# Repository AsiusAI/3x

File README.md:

# Asius 3X

```
git clone https://github.com/AsiusAI/3x
cd 3x
git submodule update --init --recursive
```

## Install ubuntu rockchip

https://github.com/Joshua-Riek/ubuntu-rockchip/releases/download/v2.4.0/ubuntu-24.04-preinstalled-server-arm64-orangepi-5-max.img.xz

flash this with Balena Etcher to the M.2 SSD. The Max version is okay for Ultra, the only difference should be the HDMI input/output port

ubuntu-24.04-preinstalled-server-arm64-orangepi-5-max.img

## Getting OV13855 camera working

See what overlays exist I used `orangepi-5-max-cam1.dtbo` overlay

```
# Check what devices exist, should have orangepi-5-max-cam1.dtbo overlay
ls /usr/lib/firmware/6.1.0-1025-rockchip/device-tree/rockchip/overlay | grep cam1

sudo nano /etc/default/u-boot

# Edit this line
# U_BOOT_FDT_OVERLAYS="device-tree/rockchip/overlay/orangepi-5-max-cam0.dtbo device-tree/rockchip/overlay/orangepi-5-max-cam1.dtbo device-tree/rockchip/overlay/orangepi-5-max-cam2.dtbo"

sudo u-boot-update

sudo reboot

# See if finds cameras
dmesg | grep ov13855
# Should show something like `Detected OV00d855 sensor, REVISION 0xb0`

# Get test image
sudo apt install v4l-utils -y
# To find the device use `v4l2-ctl --list-devices` (the first dev from rkisp_mainpath)
v4l2-ctl -d /dev/video33 --set-fmt-video=width=4224,height=3136,pixelformat='NV12' --stream-mmap --stream-skip=10 --stream-count=1 --stream-to=processed.yuv && ffmpeg -f rawvideo -pix_fmt nv12 -s 4224x3136 -i processed.yuv -y img.jpg
```

Install multimedia

sudo add-apt-repository ppa:liujianfeng1994/rockchip-multimedia
sudo apt update
sudo apt install rockchip-multimedia-config

sudo add-apt-repository ppa:jjriek/rockchip-multimedia
sudo apt update
sudo apt install camera-engine-rkaiq-rk3588

## For building Armbian OS

```
git clone https://github.com/armbian/build && cd armbian-build

./compile.sh BOARD=orangepi5-max RELEASE=noble BUILD_DESKTOP=yes DESKTOP_ENVIRONMENT=xfce DESKTOP_APPGROUPS_SELECTED='' DESKTOP_ENVIRONMENT_CONFIG_NAME=config_base BRANCH=vendor NETWORKING_STACK="network-manager" PREFER_DOCKER=no KERNEL_CONFIGURE=no
sudo dd if=output/images/Armbian-unofficial_25.11.0-trunk_Orangepi5-max_noble_vendor_6.1.115_xfce_desktop.img of=/dev/sda bs=4M status=progress conv=fsync
```

## A

cp orangepi-5-imx415-c1.dtbo /usr/lib/firmware/6.1.0-1025-rockchip/device-tree/rockchip/overlay

/usr/lib/firmware/6.1.0-1025-rockchip/device-tree/rockchip/rk3588-orangepi-5-max.dtb

device-tree/rockchip/overlay/orangepi-5-max-cam0.dtbo
device-tree/rockchip/overlay/orangepi-5-max-cam1.dtbo
device-tree/rockchip/overlay/orangepi-5-max-cam2.dtbo

sudo ./build.sh --suite noble --flavor desktop --board orangepi-5-max

## Getting openpilot to work

./tools/op.sh setup

./tools/op.sh venv

sudo apt update
sudo apt install libx11-dev libxcursor-dev libxrandr-dev libxi-dev libxinerama-dev
cd ~/3x/openpilot/third_party/raylib && ./build.sh

./tools/op.sh build

./launch_openpilot.sh

## OP working

sudo apt update

git clone https://github.com/asius.ai/3x
cd 3x
git submodule update --init --recursive openpilot
cd openpilot
./tools/op.sh setup
./tools/op.sh venv

sudo apt install libx11-dev libxcursor-dev libxrandr-dev libxi-dev libxinerama-dev
./third_party/raylib/build.sh

./tools/op.sh build

mkdir -p /home/orangepi/.comma/persist/comma/ && ssh-keygen -t rsa -N "" -f /home/orangepi/.comma/persist/comma/id_rsa

sudo apt install tmux

sudo mkdir /data && sudo chown ubuntu /data

sudo apt install xserver-xorg openbox xterm mesa-utils xinit

# tinygrad GPU=1 (on armbian)

wget -qO - https://download.opensuse.org/repositories/home:/amazingfate:/panfork-mesa/Debian_12/Release.key | sudo gpg --dearmor -o /etc/apt/trusted.gpg.d/panfork-mesa.gpg

echo "deb [trusted=yes] https://download.opensuse.org/repositories/home:/amazingfate:/panfork-mesa/Debian_12/ /" | sudo tee /etc/apt/sources.list.d/panfork-mesa.list

or `sudo add-apt-repository ppa:liujianfeng1994/panfork-mesa` ???

sudo apt update

sudo apt install mali-g610-firmware libmali-g610-x11

clinfo

# OS problems

## Orange Pi 1.0.0 Jammy with Linux 5.10.160-rockchip-rk3588 from OrangePi website

Pros:
- desktop with display works
- openpilot with panda works
- GPU=1 works in tinygrad

Cons:
- can't get any image from cameras, but they are recognized in dmesg
- larger OS
- no way to build it myself
- no community support

## ubuntu-rockchip

Pros:
- can build it myself (although it takes very long)
- cameras work fine, even IMX415
- not sure but maybe even openpilot worked

Cons:
- development stopped
- large OS
- build

## Armbian

Pros:
- build easy and fast
- small OS
- will receive updates
- openpilot works with webcam, GPU=1 works

Cons:
- cameras not working (because rkif and rkisp don't exist)

## RKNN yolov8 example working

cd ~/rknn_model_zoo/examples/yolov8

pip install rknn-toolkit2

./model/download_model.sh

cd python && python convert.py ../model/yolov8n.onnx rk3588

wget https://github.com/rockchip-linux/rknpu2/raw/refs/heads/master/runtime/RK3588/Linux/librknn_api/aarch64/librknnrt.so && sudo mv librknnrt.so /usr/lib/

python yolov8.py --model_path ../model/yolov8.rknn --target rk3588

output: ~/rknn_model_zoo/examples/yolov8/result.png

## Armbian camera support is broken

see these issues:
https://github.com/armbian/linux-rockchip/issues/164
https://github.com/armbian/linux-rockchip/issues/246
https://forum.radxa.com/t/dev-video-01/20490/42

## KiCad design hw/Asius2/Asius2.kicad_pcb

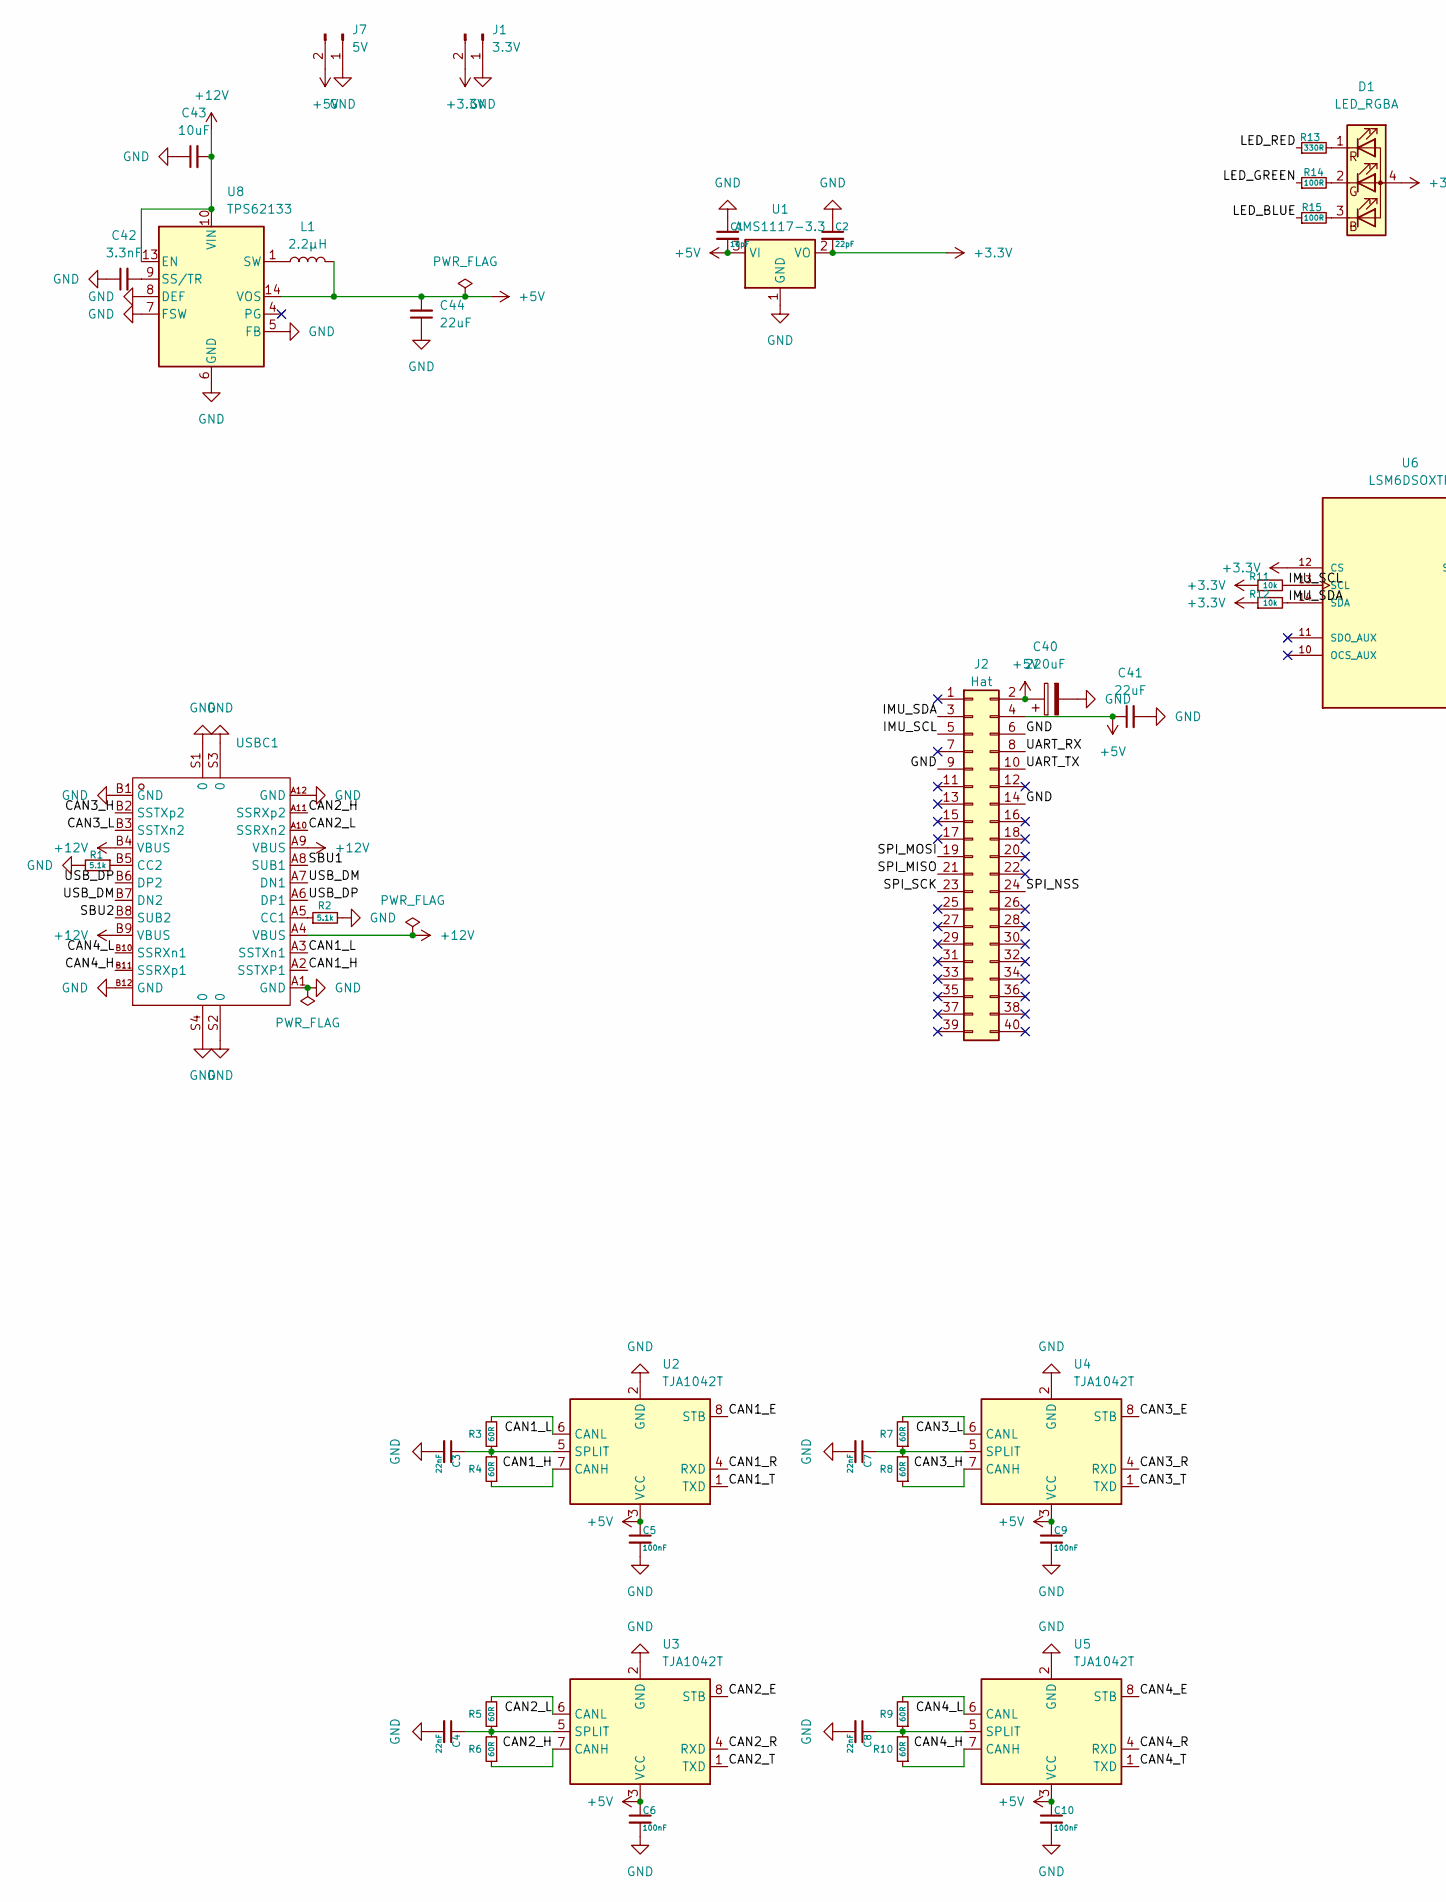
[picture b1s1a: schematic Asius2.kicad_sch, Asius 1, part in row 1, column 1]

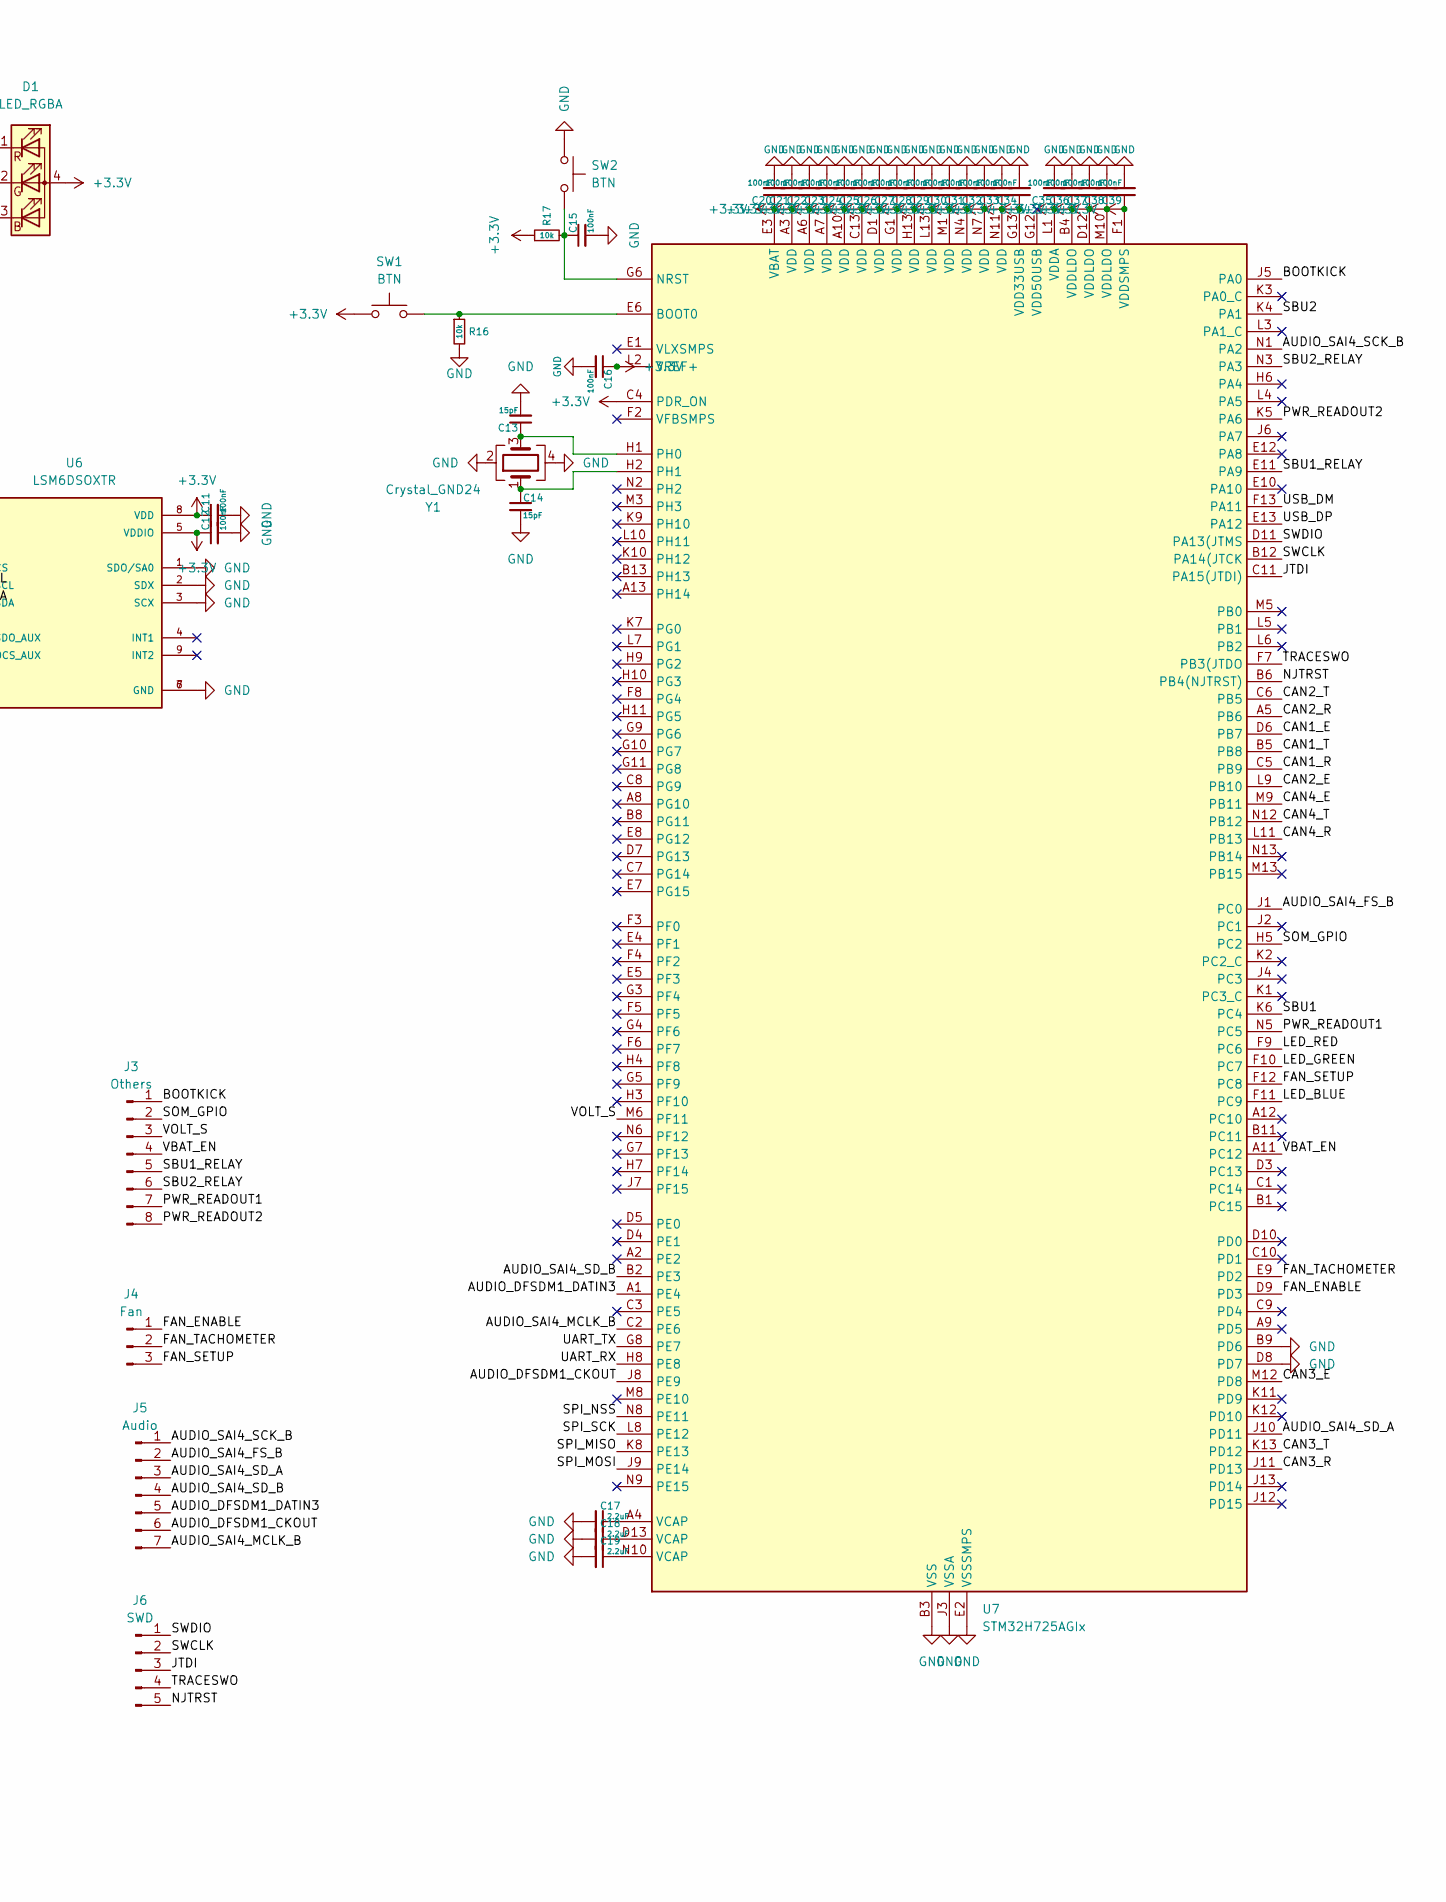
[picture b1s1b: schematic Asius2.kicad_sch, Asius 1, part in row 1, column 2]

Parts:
C1: 10pF; C_0603_1608Metric; MFR.Part # CC0603JRNPO9BN100; JLCPCB Part # C106245
C2: 22pF; C_0603_1608Metric; MFR.Part # CC0603JRNPO9BN220; JLCPCB Part # C105620
C3, C4, C7, C8: 22nF; C_0603_1608Metric; MFR.Part # CC0603KRX7R8BB223; JLCPCB Part # C106217
C5, C6, C9, C10, C11, C12, C15, C16, C20, C21, C22, C23, C24, C25, C26, C27, C28, C29, C30, C31, C32, C33, C34, C35, C36, C37, C38, C39: 100nF; C_0603_1608Metric; MFR.Part # CC0603KRX7R9BB104; JLCPCB Part # C14663
C13, C14: 15pF; C_0603_1608Metric; MFR.Part # CC0603JRNPO9BN150; JLCPCB Part # C107037
C17, C18, C19: 2.2uF; C_0603_1608Metric; MFR.Part # CC0603KRX5R6BB225; JLCPCB Part # C106213
C40: 220uF; CP_Elec_6.3x5.4; MFR.Part # RVT1A221M0605; JLCPCB Part # C3345
C41, C44: 22uF; C_0603_1608Metric; MFR.Part # CC0603MRX5R5BB226; JLCPCB Part # C109448
C42: 3.3nF; C_0603_1608Metric; MFR.Part # CC0603JRNPO9BN332; JLCPCB Part # C107048
C43: 10uF; C_0805_2012Metric; MFR.Part # CC0805KKX5R8BB106; JLCPCB Part # C89831
D1: LED_RGBA; LED_RGB_1210; MFR.Part # SZYY1209RGB-B 4pin; JLCPCB Part # C3029073
J1: 3.3V; PinHeader_1x02_P2.54mm_Vertical
J2: Hat; PinHeader_2x20_P2.54mm_Vertical
J3: Others; PinHeader_1x08_P2.54mm_Vertical
J4: Fan; PinHeader_1x03_P2.54mm_Vertical
J5: Audio; PinHeader_1x07_P2.54mm_Vertical
J6: SWD; PinHeader_1x05_P2.54mm_Vertical
J7: 5V; PinHeader_1x02_P2.54mm_Vertical
L1: 2.2µH; L_Coilcraft_XxL4020; MFR.Part # XFL4020-222MEC; JLCPCB Part # C122469
R1, R2: 5.1k; R_0603_1608Metric; MFR.Part # RT0603BRD075K1L; JLCPCB Part # C122969
R3, R4, R5, R6, R7, R8, R9, R10: 60R; R_0603_1608Metric; MFR.Part # RC0603FR-0762RL; JLCPCB Part # C245989
R11, R12, R16, R17: 10k; R_0603_1608Metric; MFR.Part # RC0603FR-0710KL; JLCPCB Part # C98220
R13: 330R; R_0603_1608Metric; MFR.Part # RC0603FR-07330RL; JLCPCB Part # C105881
R14, R15: 100R; R_0603_1608Metric; MFR.Part # RC0603FR-07100RL; JLCPCB Part # C105588
SW1, SW2: BTN; SW_SPST_EVQP2_ShortPushTravel_H2.1mm; MFR.Part # EVQP2R02M; JLCPCB Part # C79161
U1: AMS1117-3.3; SOT-223-3_TabPin2; MFR.Part # AMS1117-3.3; JLCPCB Part # C6186
U2, U3, U4, U5: TJA1042T; SOIC-8_3.9x4.9mm_P1.27mm; MFR.Part # TJA1042T/1J; JLCPCB Part # C53670
U6: LSM6DSOXTR; PQFN50P250X300X86-14N; PARTREV 3.0; JLCPCB Part # C481766
U7: STM32H725AGIx; UFBGA-169_7x7mm_Layout13x13_P0.5mm; MFR.Part # STM32H725AGI6; JLCPCB Part # C730148
U8: TPS62133; VQFN-16-1EP_3x3mm_P0.5mm_EP1.68x1.68mm_ThermalVias; MFR.Part # TPS62133RGTR; JLCPCB Part # C73973
USBC1: USB-C-SMD_TYPE-C-USB-20; Manufacturer Part TYPE-C-31-M-04; LCSC Part Name Type-C 母
Y1: Crystal_GND24; Crystal_SMD_3225-4Pin_3.2x2.5mm; MFR.Part # X322525MOB4SI; JLCPCB Part # C9006

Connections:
+3.3V: C2.2, C11.1, C12.1, C16.1, C20.1, C21.1, C22.1, C23.1, C24.1, C25.1, C26.1, C27.1, C28.1, C29.1, C30.1, C31.1, C32.1, C33.1, C34.1, C35.1, C36.1, C37.1, C38.1, C39.1, D1.4 (A), J1.2, R11.1, R12.1, R17.1, SW1.1, U1.2 (VO), U6.5 (VDDIO), U6.8 (VDD), U6.12 (CS), U7.A3 (VDD), U7.A6 (VDD), U7.A7 (VDD), U7.A10 (VDD), U7.B4 (VDDLDO), U7.C4 (PDR_ON), U7.C13 (VDD), U7.D1 (VDD), U7.D12 (VDDLDO), U7.E3 (VBAT), U7.F1 (VDDSMPS), U7.G1 (VDD), U7.G13 (VDD33USB), U7.H13 (VDD), U7.L1 (VDDA), U7.L2 (VREF+), U7.L13 (VDD), U7.M1 (VDD), U7.M10 (VDDLDO), U7.N4 (VDD), U7.N7 (VDD), U7.N11 (VDD)
+5V: C1.2, C5.1, C6.1, C9.1, C10.1, C40.1, C41.1, C44.2, J2.2, J2.4, J7.2, L1.2, U1.3 (VI), U2.3 (VCC), U3.3 (VCC), U4.3 (VCC), U5.3 (VCC), U8.14 (VOS)
+12V: C43.2, U8.10 (VIN), U8.11 (VIN), U8.12 (VIN), U8.13 (EN), USBC1.A4 (VBUS), USBC1.A9 (VBUS), USBC1.B4 (VBUS), USBC1.B9 (VBUS)
/AUDIO_DFSDM1_CKOUT: J5.6, U7.J8 (PE9)
/AUDIO_DFSDM1_DATIN3: J5.5, U7.A1 (PE4)
/AUDIO_SAI4_FS_B: J5.2, U7.J1 (PC0)
/AUDIO_SAI4_MCLK_B: J5.7, U7.C2 (PE6)
/AUDIO_SAI4_SCK_B: J5.1, U7.N1 (PA2)
/AUDIO_SAI4_SD_A: J5.3, U7.J10 (PD11)
/AUDIO_SAI4_SD_B: J5.4, U7.B2 (PE3)
/BOOTKICK: J3.1, U7.J5 (PA0)
/CAN1_E: U2.8 (STB), U7.D6 (PB7)
/CAN1_H: R4.1, U2.7 (CANH), USBC1.A2 (SSTXP1)
/CAN1_L: R3.2, U2.6 (CANL), USBC1.A3 (SSTXn1)
/CAN1_R: U2.4 (RXD), U7.C5 (PB9)
/CAN1_T: U2.1 (TXD), U7.B5 (PB8)
/CAN2_E: U3.8 (STB), U7.L9 (PB10)
/CAN2_H: R6.1, U3.7 (CANH), USBC1.A11 (SSRXp2)
/CAN2_L: R5.2, U3.6 (CANL), USBC1.A10 (SSRXn2)
/CAN2_R: U3.4 (RXD), U7.A5 (PB6)
/CAN2_T: U3.1 (TXD), U7.C6 (PB5)
/CAN3_E: U4.8 (STB), U7.M12 (PD8)
/CAN3_H: R8.1, U4.7 (CANH), USBC1.B2 (SSTXp2)
/CAN3_L: R7.2, U4.6 (CANL), USBC1.B3 (SSTXn2)
/CAN3_R: U4.4 (RXD), U7.J11 (PD13)
/CAN3_T: U4.1 (TXD), U7.K13 (PD12)
/CAN4_E: U5.8 (STB), U7.M9 (PB11)
/CAN4_H: R10.1, U5.7 (CANH), USBC1.B11 (SSRXp1)
/CAN4_L: R9.2, U5.6 (CANL), USBC1.B10 (SSRXn1)
/CAN4_R: U5.4 (RXD), U7.L11 (PB13)
/CAN4_T: U5.1 (TXD), U7.N12 (PB12)
/FAN_ENABLE: J4.1, U7.D9 (PD3)
/FAN_SETUP: J4.3, U7.F12 (PC8)
/FAN_TACHOMETER: J4.2, U7.E9 (PD2)
/IMU_SCL: J2.5, R11.2, U6.13 (SCL)
/IMU_SDA: J2.3, R12.2, U6.14 (SDA)
/JTDI: J6.3, U7.C11 (PA15(JTDI))
/LED_BLUE: R15.1, U7.F11 (PC9)
/LED_GREEN: R14.1, U7.F10 (PC7)
/LED_RED: R13.1, U7.F9 (PC6)
/NJTRST: J6.5, U7.B6 (PB4(NJTRST))
/PWR_READOUT1: J3.7, U7.N5 (PC5)
/PWR_READOUT2: J3.8, U7.K5 (PA6)
/SBU1: U7.K6 (PC4), USBC1.A8 (SUB1)
/SBU1_RELAY: J3.5, U7.E11 (PA9)
/SBU2: U7.K4 (PA1), USBC1.B8 (SUB2)
/SBU2_RELAY: J3.6, U7.N3 (PA3)
/SOM_GPIO: J3.2, U7.H5 (PC2)
/SPI_MISO: J2.21, U7.K8 (PE13)
/SPI_MOSI: J2.19, U7.J9 (PE14)
/SPI_NSS: J2.24, U7.N8 (PE11)
/SPI_SCK: J2.23, U7.L8 (PE12)
/SWCLK: J6.2, U7.B12 (PA14(JTCK)
/SWDIO: J6.1, U7.D11 (PA13(JTMS)
/TRACESWO: J6.4, U7.F7 (PB3(JTDO)
/UART_RX: J2.8, U7.H8 (PE8)
/UART_TX: J2.10, U7.G8 (PE7)
/USB_DM: U7.F13 (PA11), USBC1.A7 (DN1), USBC1.B7 (DN2)
/USB_DP: U7.E13 (PA12), USBC1.A6 (DP1), USBC1.B6 (DP2)
/VBAT_EN: J3.4, U7.A11 (PC12)
/VOLT_S: J3.3, U7.M6 (PF11)
GND: C1.1, C2.1, C3.2, C4.2, C5.2, C6.2, C7.2, C8.2, C9.2, C10.2, C11.2, C12.2, C13.2, C14.2, C15.2, C16.2, C17.2, C18.2, C19.2, C20.2, C21.2, C22.2, C23.2, C24.2, C25.2, C26.2, C27.2, C28.2, C29.2, C30.2, C31.2, C32.2, C33.2, C34.2, C35.2, C36.2, C37.2, C38.2, C39.2, C40.2, C41.2, C42.1, C43.1, C44.1, J1.1, J2.6, J2.9, J2.14, J7.1, R1.2, R2.2, R16.2, SW2.1, U1.1 (GND), U2.2 (GND), U3.2 (GND), U4.2 (GND), U5.2 (GND), U6.1 (SDO/SA0), U6.2 (SDX), U6.3 (SCX), U6.6 (GND), U6.7 (GND), U7.B3 (VSS), U7.B7 (VSS), U7.B9 (PD6), U7.B10 (VSS), U7.C12 (VSS), U7.D2 (VSS), U7.D8 (PD7), U7.E2 (VSSSMPS), U7.G2 (VSS), U7.H12 (VSS), U7.J3 (VSSA), U7.L12 (VSS), U7.M2 (VSS), U7.M4 (VSS), U7.M7 (VSS), U7.M11 (VSS), U8.5 (FB), U8.6 (GND), U8.7 (FSW), U8.8 (DEF), U8.15 (GND), U8.16 (GND), U8.17 (GND), USBC1.A1 (GND), USBC1.A12 (GND), USBC1.B1 (GND), USBC1.B12 (GND), USBC1.S1 (0), USBC1.S2 (0), USBC1.S3 (0), USBC1.S4 (0), Y1.2, Y1.4
unnamed: C17.1, U7.A4 (VCAP)
unnamed: C18.1, U7.D13 (VCAP)
unnamed: C19.1, U7.N10 (VCAP)
unnamed: D1.3 (BK), R15.2
unnamed: D1.2 (GK), R14.2
unnamed: D1.1 (RK), R13.2
unnamed: L1.1, U8.1 (SW), U8.2 (SW), U8.3 (SW)
unnamed: C3.1, R3.1, R4.2, U2.5 (SPLIT)
unnamed: C4.1, R5.1, R6.2, U3.5 (SPLIT)
unnamed: C7.1, R7.1, R8.2, U4.5 (SPLIT)
unnamed: C8.1, R9.1, R10.2, U5.5 (SPLIT)
unnamed: R16.1, SW1.2, U7.E6 (BOOT0)
unnamed: C15.1, R17.2, SW2.2, U7.G6 (NRST)
unnamed: C13.1, U7.H1 (PH0), Y1.3
unnamed: C14.1, U7.H2 (PH1), Y1.1
unnamed: C42.2, U8.9 (SS/TR)
unnamed: R2.1, USBC1.A5 (CC1)
unnamed: R1.1, USBC1.B5 (CC2)

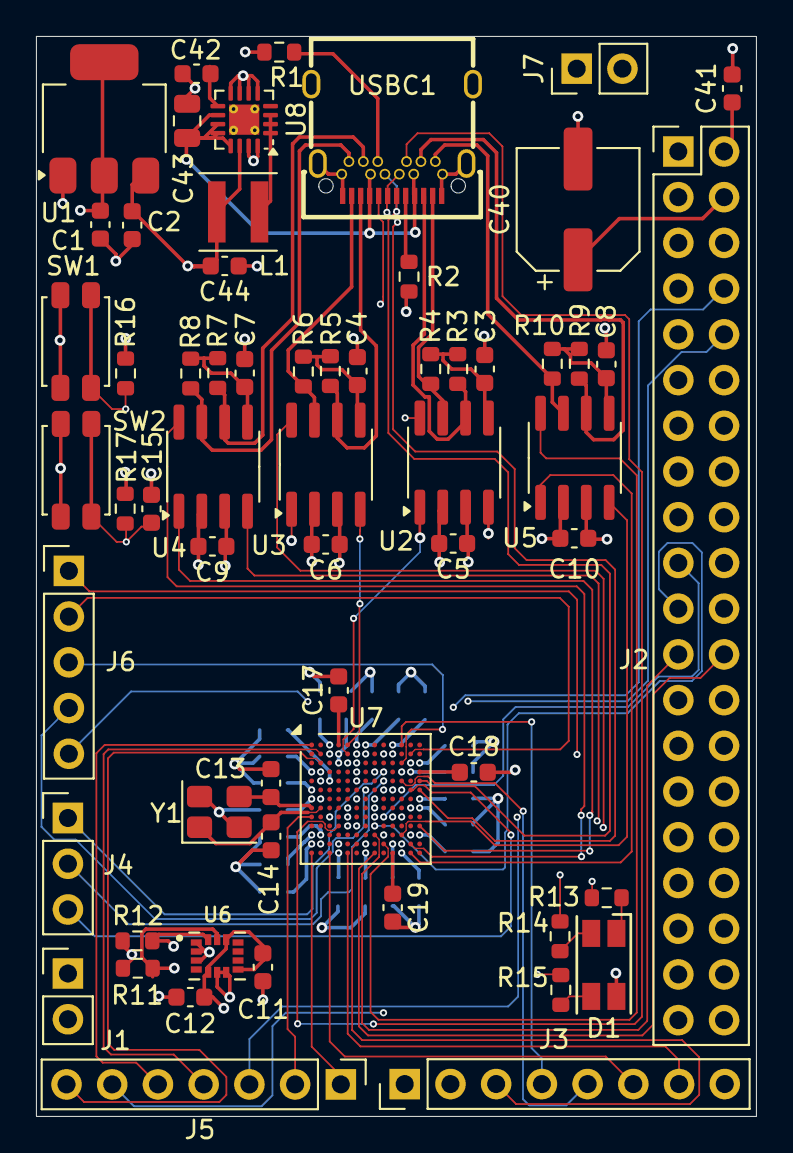
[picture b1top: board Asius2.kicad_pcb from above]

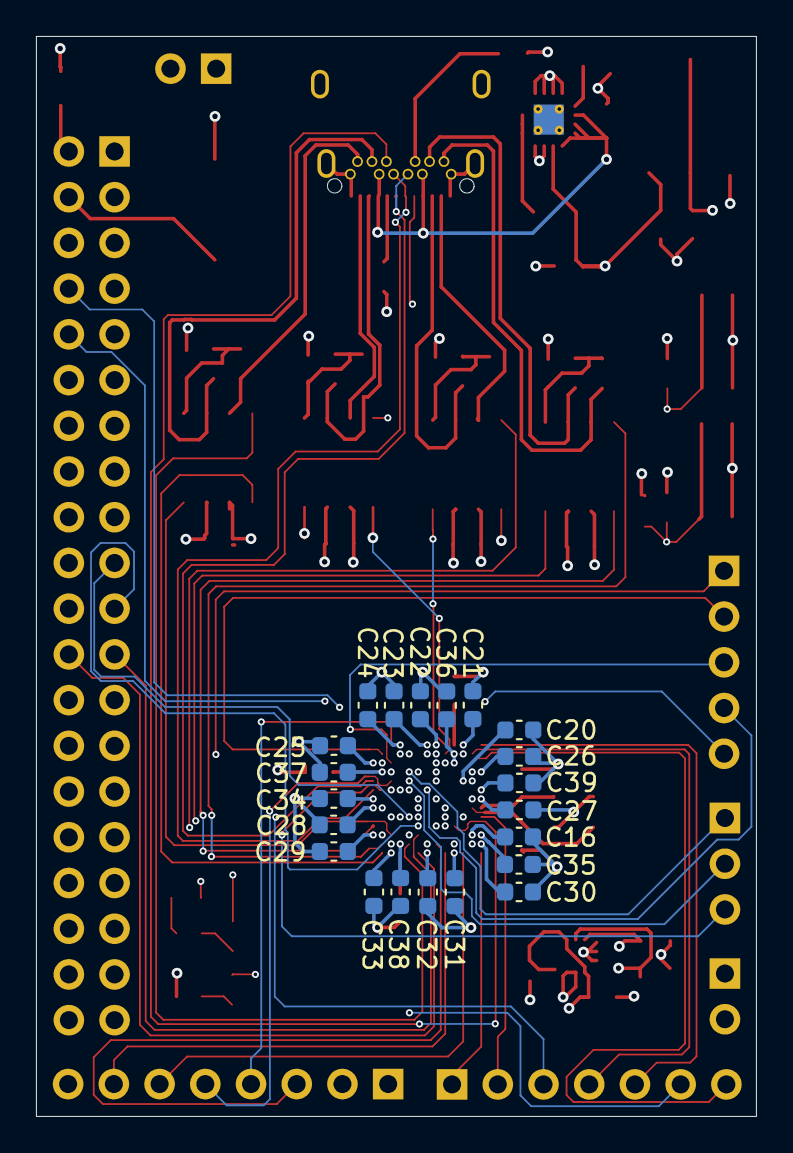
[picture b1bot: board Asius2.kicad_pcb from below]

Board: 6 copper layers, 40.0 x 60.0 mm, 82 parts (21 on the bottom side), 80 nets.

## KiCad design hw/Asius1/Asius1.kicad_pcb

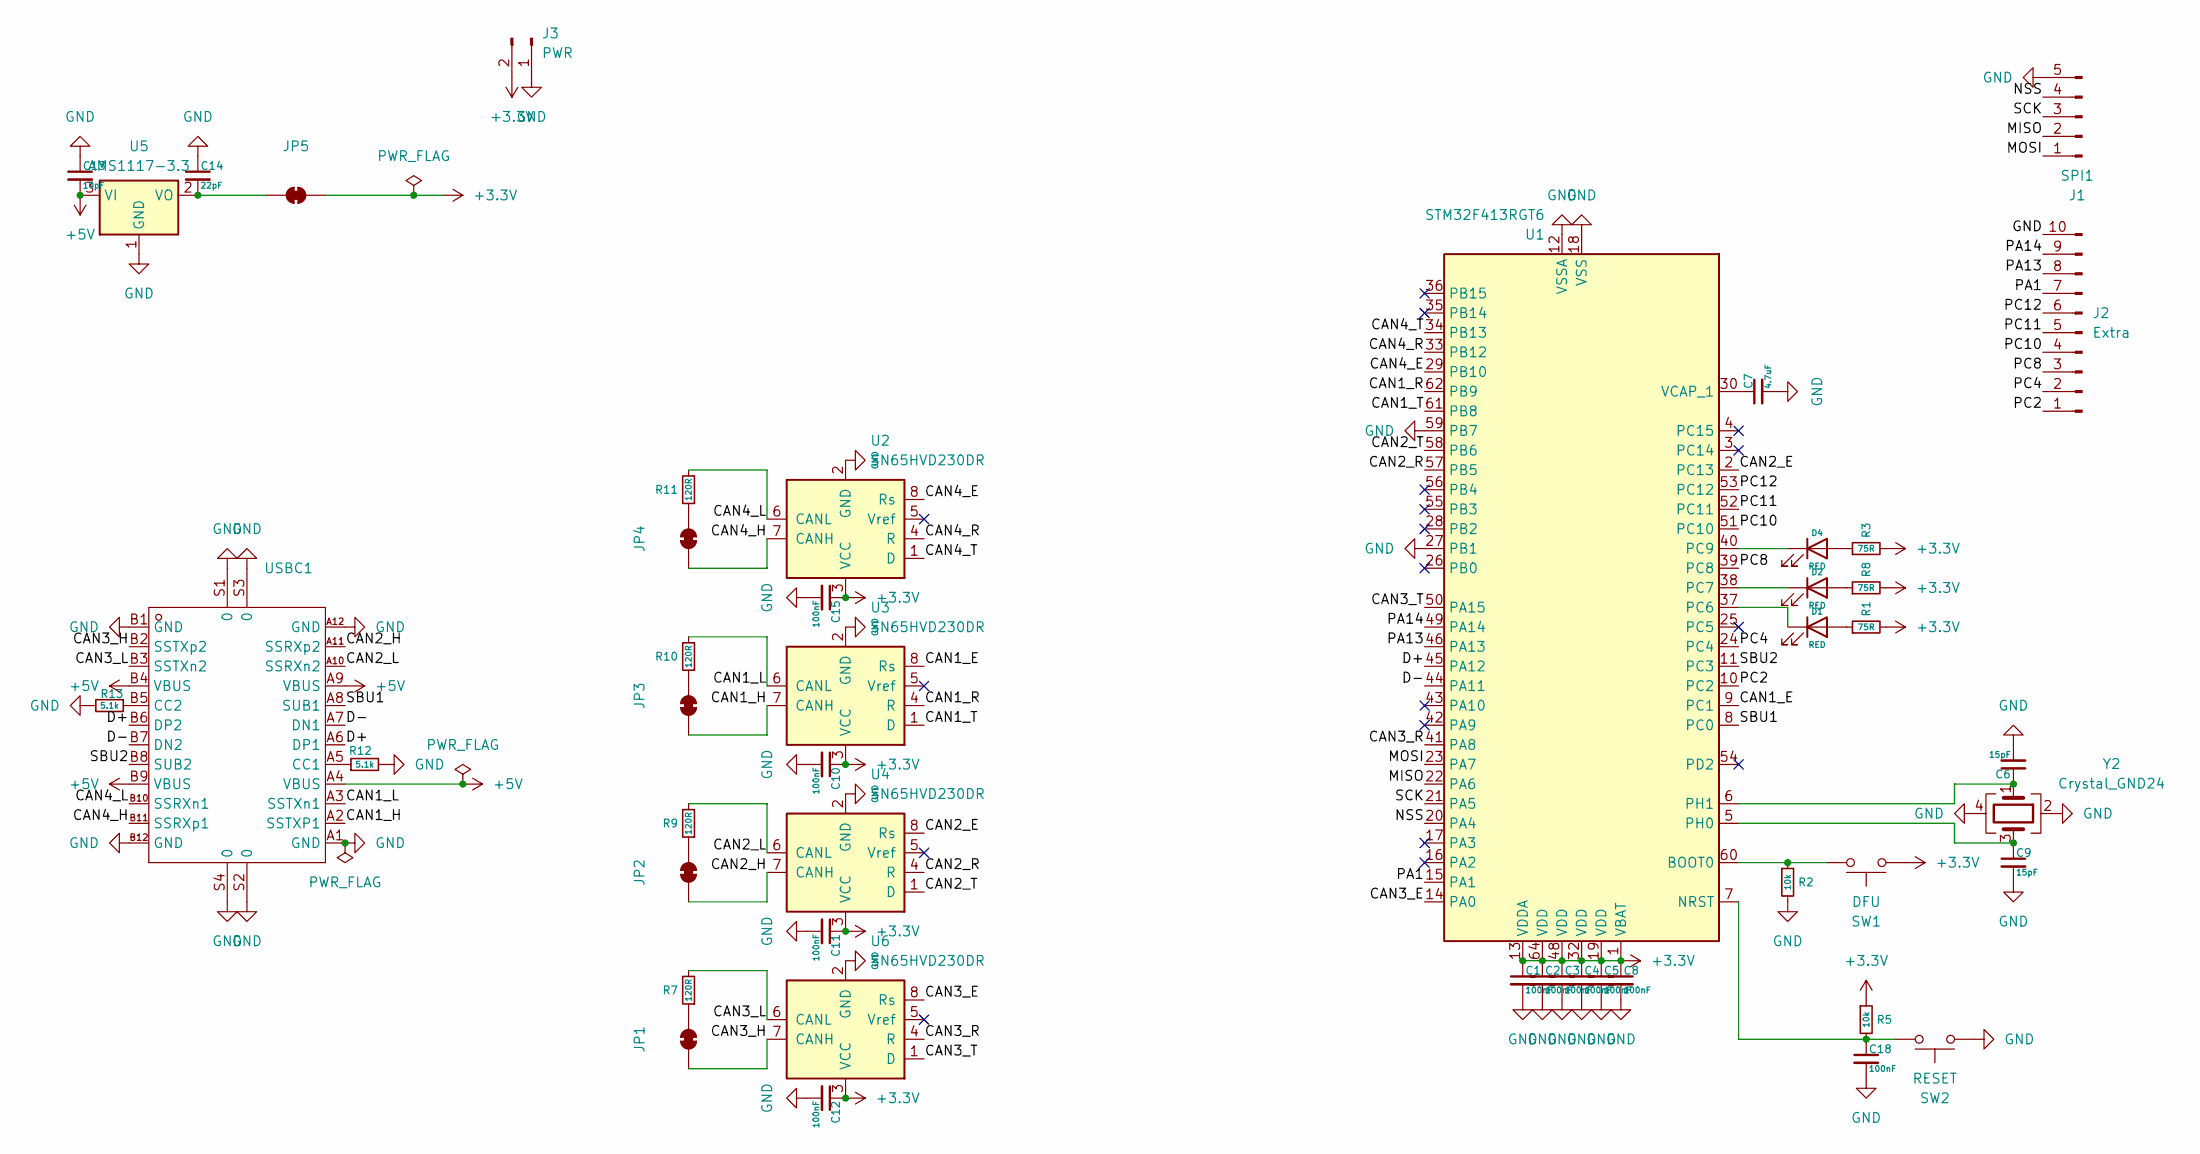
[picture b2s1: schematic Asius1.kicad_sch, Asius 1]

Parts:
C1, C2, C3, C4, C5, C8, C10, C11, C12, C15, C18: 100nF; C_0603_1608Metric; MPN CC0603KRX7R9BB104
C6, C9: 15pF; C_0603_1608Metric; MPN CC0603JRNPO9BN150
C7: 4.7uF; C_0603_1608Metric; MPN CC0603KRX5R7BB475
C13: 10pF; C_0603_1608Metric; MPN CC0603JRNPO9BN100
C14: 22pF; C_0603_1608Metric; MPN CC0603JRNPO9BN220
D1, D2, D4: RED; LED_0603_1608Metric; MPN KT-0603R
J1: SPI1; PinHeader_1x05_P2.54mm_Vertical
J2: Extra; PinHeader_1x10_P2.54mm_Vertical
J3: PWR; PinHeader_1x02_P2.54mm_Vertical
JP1, JP2, JP3, JP4, JP5: SolderJumper-2_P1.3mm_Bridged_RoundedPad1.0x1.5mm
R1, R3, R8: 75R; R_0603_1608Metric; MPN RC0603FR-0775RL
R2, R5: 10k; R_0603_1608Metric; MPN RC0603FR-0710KL
R7, R9, R10, R11: 120R; R_0603_1608Metric; MPN RC0603FR-07120RL
R12, R13: 5.1k; R_0603_1608Metric; MPN RC0603FR-075K1L
SW1: DFU; SW_SPST_PTS645Sx43SMTR92; MPN PTS645SK43SMTR92LFS
SW2: RESET; SW_SPST_PTS645Sx43SMTR92; MPN PTS645SK43SMTR92LFS
U1: STM32F413RGT6; LQFP-64_10x10mm_P0.5mm; MPN STM32F413RGT6
U2, U3, U4, U6: SN65HVD230DR; SOIC-8_3.9x4.9mm_P1.27mm; MPN SN65HVD230DR
U5: AMS1117-3.3; SOT-223-3_TabPin2; MPN AMS1117-3.3
USBC1: USB-C-SMD_TYPE-C-USB-20; Manufacturer Part TYPE-C-31-M-04; LCSC Part Name Type-C 母
Y2: Crystal_GND24; Crystal_SMD_3225-4Pin_3.2x2.5mm; MPN X322516MOB4SI

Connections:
+3.3V: C1.1, C2.1, C3.1, C4.1, C5.1, C8.1, C10.1, C11.1, C12.1, C15.1, J3.2, JP5.1 (A), R1.2, R3.2, R5.1, R8.2, SW1.1, U1.1 (VBAT), U1.13 (VDDA), U1.19 (VDD), U1.32 (VDD), U1.48 (VDD), U1.64 (VDD), U2.3 (VCC), U3.3 (VCC), U4.3 (VCC), U6.3 (VCC)
+5V: C13.2, U5.3 (VI), USBC1.A4 (VBUS), USBC1.A9 (VBUS), USBC1.B4 (VBUS), USBC1.B9 (VBUS)
/CAN1_E: U1.9 (PC1), U3.8 (Rs)
/CAN1_H: JP3.1 (A), U3.7 (CANH), USBC1.A2 (SSTXP1)
/CAN1_L: R10.2, U3.6 (CANL), USBC1.A3 (SSTXn1)
/CAN1_R: U1.62 (PB9), U3.4 (R)
/CAN1_T: U1.61 (PB8), U3.1 (D)
/CAN2_E: U1.2 (PC13), U4.8 (Rs)
/CAN2_H: JP2.1 (A), U4.7 (CANH), USBC1.A11 (SSRXp2)
/CAN2_L: R9.2, U4.6 (CANL), USBC1.A10 (SSRXn2)
/CAN2_R: U1.57 (PB5), U4.4 (R)
/CAN2_T: U1.58 (PB6), U4.1 (D)
/CAN3_E: U1.14 (PA0), U6.8 (Rs)
/CAN3_H: JP1.1 (A), U6.7 (CANH), USBC1.B2 (SSTXp2)
/CAN3_L: R7.2, U6.6 (CANL), USBC1.B3 (SSTXn2)
/CAN3_R: U1.41 (PA8), U6.4 (R)
/CAN3_T: U1.50 (PA15), U6.1 (D)
/CAN4_E: U1.29 (PB10), U2.8 (Rs)
/CAN4_H: JP4.1 (A), U2.7 (CANH), USBC1.B11 (SSRXp1)
/CAN4_L: R11.2, U2.6 (CANL), USBC1.B10 (SSRXn1)
/CAN4_R: U1.33 (PB12), U2.4 (R)
/CAN4_T: U1.34 (PB13), U2.1 (D)
/D+: U1.45 (PA12), USBC1.A6 (DP1), USBC1.B6 (DP2)
/D-: U1.44 (PA11), USBC1.A7 (DN1), USBC1.B7 (DN2)
/MISO: J1.2, U1.22 (PA6)
/MOSI: J1.1, U1.23 (PA7)
/NSS: J1.4, U1.20 (PA4)
/PA1: J2.7, U1.15 (PA1)
/PA13: J2.8, U1.46 (PA13)
/PA14: J2.9, U1.49 (PA14)
/PC2: J2.1, U1.10 (PC2)
/PC4: J2.2, U1.24 (PC4)
/PC8: J2.3, U1.39 (PC8)
/PC10: J2.4, U1.51 (PC10)
/PC11: J2.5, U1.52 (PC11)
/PC12: J2.6, U1.53 (PC12)
/SBU1: U1.8 (PC0), USBC1.A8 (SUB1)
/SBU2: U1.11 (PC3), USBC1.B8 (SUB2)
/SCK: J1.3, U1.21 (PA5)
GND: C1.2, C2.2, C3.2, C4.2, C5.2, C6.2, C7.2, C8.2, C9.2, C10.2, C11.2, C12.2, C13.1, C14.1, C15.2, C18.2, J1.5, J2.10, J3.1, R2.2, R12.2, R13.2, SW2.1, U1.12 (VSSA), U1.18 (VSS), U1.27 (PB1), U1.31 (VSS), U1.47 (VSS), U1.59 (PB7), U1.63 (VSS), U2.2 (GND), U3.2 (GND), U4.2 (GND), U5.1 (GND), U6.2 (GND), USBC1.A1 (GND), USBC1.A12 (GND), USBC1.B1 (GND), USBC1.B12 (GND), USBC1.S1 (0), USBC1.S2 (0), USBC1.S3 (0), USBC1.S4 (0), Y2.2, Y2.4
unnamed: D1.2 (A), R1.1
unnamed: D1.1 (K), U1.37 (PC6)
unnamed: D2.2 (A), R8.1
unnamed: D2.1 (K), U1.38 (PC7)
unnamed: D4.2 (A), R3.1
unnamed: D4.1 (K), U1.40 (PC9)
unnamed: JP1.2 (B), R7.1
unnamed: JP2.2 (B), R9.1
unnamed: JP3.2 (B), R10.1
unnamed: JP4.2 (B), R11.1
unnamed: C14.2, JP5.2 (B), U5.2 (VO)
unnamed: R2.1, SW1.2, U1.60 (BOOT0)
unnamed: C18.1, R5.2, SW2.2, U1.7 (NRST)
unnamed: C9.1, U1.5 (PH0), Y2.3
unnamed: C6.1, U1.6 (PH1), Y2.1
unnamed: C7.1, U1.30 (VCAP_1)
unnamed: R12.1, USBC1.A5 (CC1)
unnamed: R13.1, USBC1.B5 (CC2)

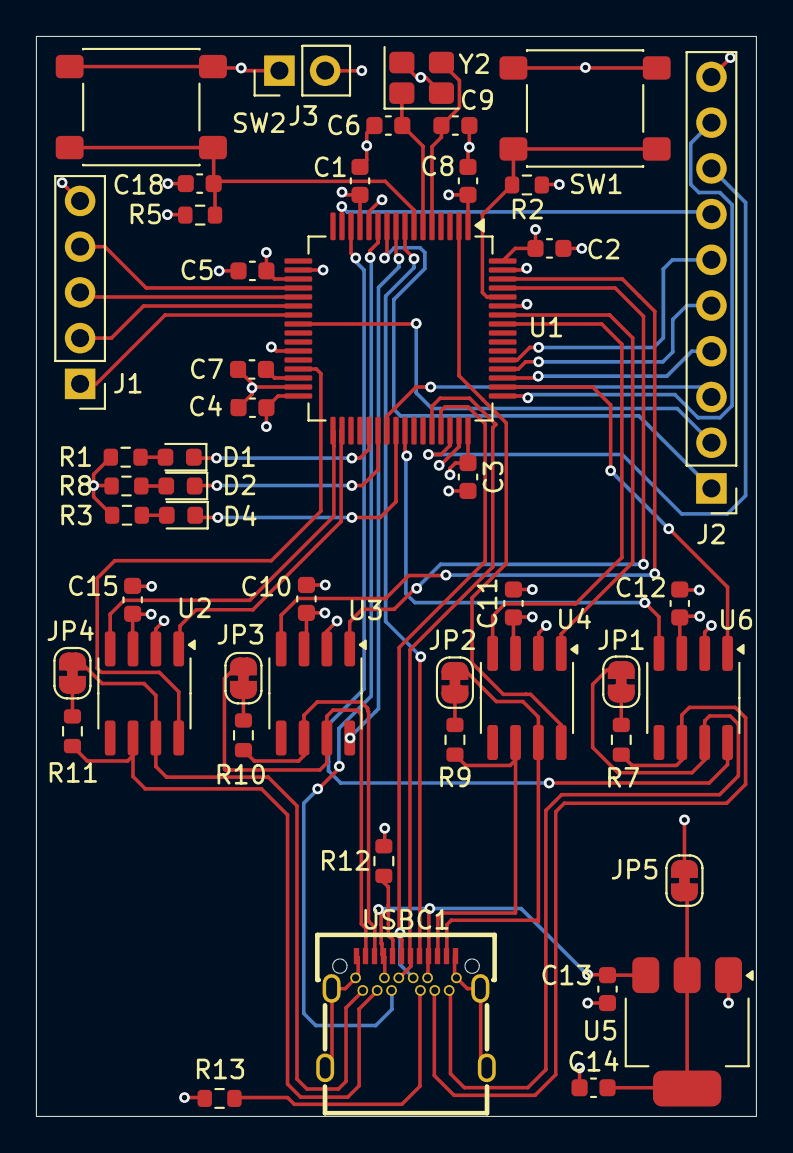
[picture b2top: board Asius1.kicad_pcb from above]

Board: 4 copper layers, 40.0 x 60.0 mm, 48 parts (0 on the bottom side), 58 nets.

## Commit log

2025-08-30 submodules
2025-08-30 readme
2025-08-30 config
2025-09-11 first pcb design
2025-09-11 remove armbian and camera instructions
2025-09-11 cam instructions
2025-09-11 copy RKPilot imx415 folder
2025-09-11 translate readme
2025-09-12 orangepi max files
2025-09-12 move
2025-09-12 imx415 working
2025-09-12 patch all cameras
2025-09-12 added linux-rockchip
2025-09-12 save
2025-09-16 armbian-build
2025-09-28 Asius2 kicad
2025-10-04 different OS options
2025-10-04 armbian desktop build
2025-10-05 GPU=1 working on armbian
2025-10-07 new build
2025-10-07 armbian kernel
2025-10-07 rk3588-orangepi-5-max-ubuntu
2025-10-08 ubuntu-rockchip dtb files
2025-10-08 logs
2025-10-12 more logs
2025-10-12 max.dtb from ubuntu-rockchip
2025-10-13 issues
